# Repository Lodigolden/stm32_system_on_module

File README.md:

# STM32H7 System-on-Module
## Overview
This STM32H7 system-on-module is everything needed to get the MCU up and running. Simply place a footprint for the board-to-board connectors on your motherboard, and use whatever pins your project needs!

## Hardware
The system-on-module is a powerful compute source with everything you need for intensive computation. Peripherals include:
- STM32H743ZGT6 32Bit MCU
- AS4C8M16SA-7TCN 128MBit SDRAM
- AT25FF161A-SSHN-T 16MBit QSPI Flash
- CP2102N-A02-GQFN20R USB-to-UART Bridge

The system on module has a point-of-load regulator (TPSM861253RDXR) to ensure stable, efficient power delivery to on-board peripherals.

## Firmware
Included in this repository is a device tree file and other necessary files for building a zephyr image. The **fw/** README.md file gives instructions for building on a Linux system.

> TODO: Write instructions for Windows use.

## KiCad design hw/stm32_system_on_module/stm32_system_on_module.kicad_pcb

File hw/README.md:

# Overview
The **pinout/** directory includes an STMCubeIDE file used to deetermine pinouts for the on-board components. If the end user doesn't wish to use Zephyr and would rather use STMCubeIDE, they can feel free to start with that folder.

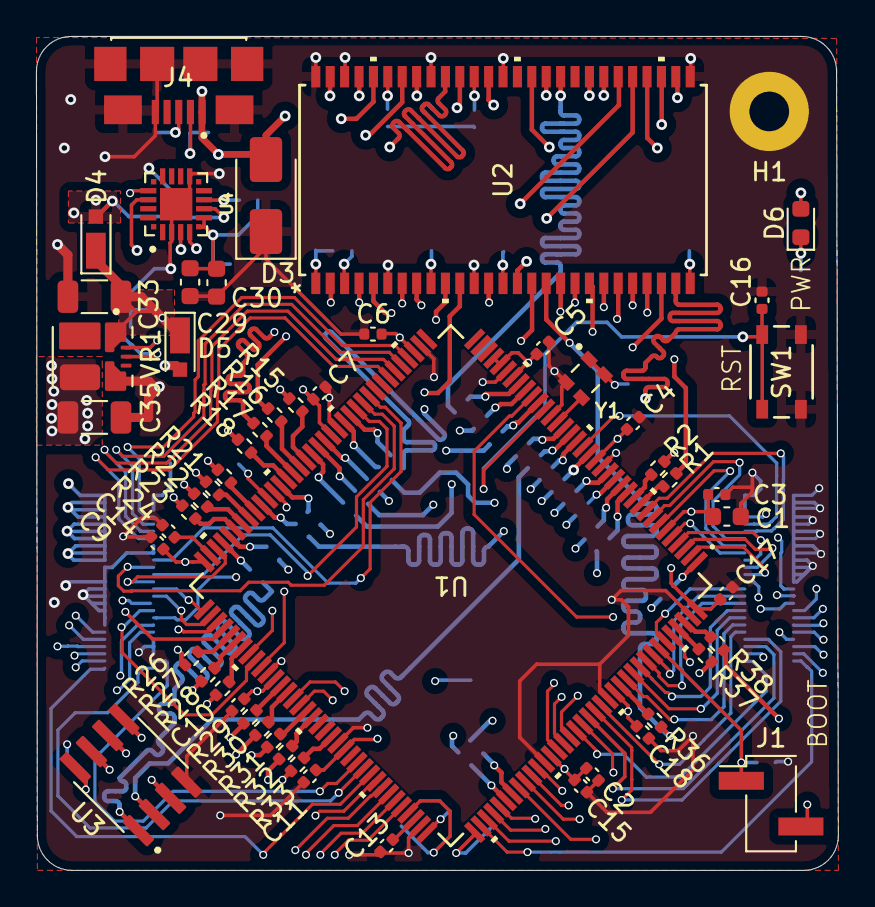
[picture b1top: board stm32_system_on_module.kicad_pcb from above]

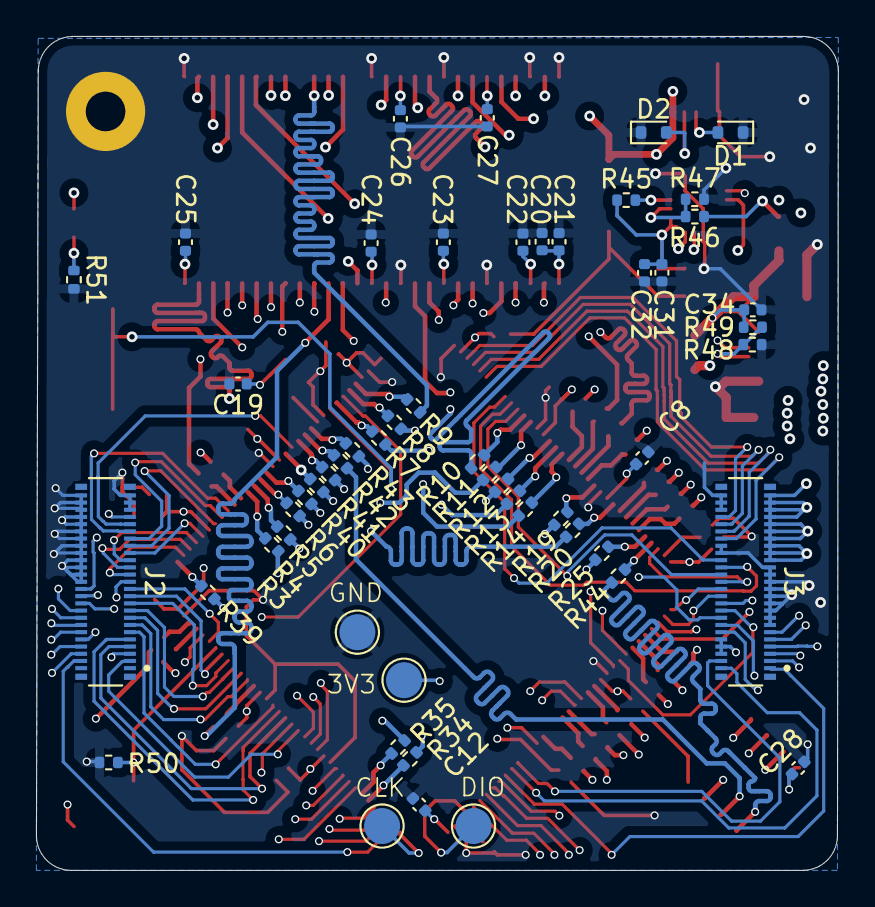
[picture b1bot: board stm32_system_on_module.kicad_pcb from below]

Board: 8 copper layers, 44.6 x 46.3 mm, 108 parts (53 on the bottom side), 163 nets.

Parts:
C1, C29, C30: 4u7; C_0603_1608Metric
C2, C20: 1u; C_0402_1005Metric
C3, C4, C5, C6, C7, C8, C9, C10, C11, C12, C13, C14, C15, C16, C17, C18, C19, C21, C22, C23, C24, C25, C26, C27, C28, C31, C32, C34: 100n; C_0402_1005Metric
C33: 10u; C_1206_3216Metric
C35: 22u; C_1206_3216Metric
D1, D2: D_TVS; D_SOD-523
D3: D_TVS; D_SMA
D4, D5: D_Schottky; D_MicroSMP_AK
D6: LED; LED_0603_1608Metric
H1: MountingHole_Pad; MountingHole_2.2mm_M2_Pad
J1: Conn_01x02_Pin; PinHeader_1x02_P2.54mm_Vertical_SMD_Pin1Left
J2, J3: DF40C-50DP-0.4V_51_; HIROSE_DF40C-50DP-0.4V_51_
J4: 10118192-0002LF; AMPHENOL_10118192-0002LF
R1, R2, R3, R4, R5, R6, R7, R8, R9, R10, R11, R12, R13, R14, R15, R16, R17, R18, R19, R20, R21, R22, R23, R24, R25, R26, R27, R28, R29, R30, R31, R32, R33, R34, R35, R36, R37, R38, R39, R40, R41, R42, R43, R44: 33; R_0402_1005Metric
R45: 1k; R_0402_1005Metric
R46: 22k1; R_0402_1005Metric
R47: 47k5; R_0402_1005Metric
R48: 4k99; R_0402_1005Metric
R49, R50: 10k; R_0402_1005Metric
R51: 330; R_0402_1005Metric
SW1: PTS810 SJK 250 SMTR LFS; PTS810_CNK
TP1, TP2, TP3, TP4: TestPoint; TestPoint_Pad_D2.0mm
U1: STM32H743ZGT6; stm32h743zgt6
U2: AS4C8M16SA-7TCN; TSOP-54_11P96X22P35_ALL
U3: AT25FF161A-SSHN-T; SOIC127P599X175-8N
U4: CP2102N-A02-GQFN20R; SILABS_CP2102N-A02-GQFN20R
VR1: TPSM861253RDXR; VREG_TPSM861253RDXR
Y1: KC2016Z8.00000C15XXK; OSC_KC2016Z8.00000C15XXK-4

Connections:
+3V3: C1.1, C2.1, C3.1, C4.1, C5.1, C6.1, C7.1, C8.1, C9.1, C10.1, C11.1, C12.1, C15.1, C17.1, C18.1, C19.1, C20.1, C21.1, C22.1, C23.1, C24.1, C25.1, C26.1, C27.1, C28.1, C29.1, C30.1, C31.1, C32.1, C35.1, D6.2 (A), J1.2, R45.1, TP3.1, U1.6 (VBAT), U1.17 (VDD), U1.30 (VDD), U1.32 (VREF+), U1.33 (VDDA), U1.39 (VDD), U1.52 (VDD), U1.62 (VDD), U1.72 (VDD), U1.84 (VDD), U1.95 (VDD33USB), U1.108 (VDD), U1.121 (VDD), U1.131 (VDD), U1.144 (VDD), U2.1 (VDD), U2.3 (VDDQ), U2.9 (VDDQ), U2.14 (VDD), U2.27 (VDD), U2.43 (VDDQ), U2.49 (VDDQ), U3.8 (VCC), U4.6 (VDD), U4.7 (VREGIN), VR1.3 (VOUT), VR1.7 (VOS), Y1.1 (INH), Y1.4 (VCC)
+5V: D3.2 (A2), D4.2 (A), J4.1 (VCC), R46.1
/Input/USB.D+: D1.2 (A2), J4.3 (D+), U4.4 (D+)
/Input/USB.D-: D2.2 (A2), J4.2 (D-), U4.5 (D-)
/MCU/BOOT: J1.1, R50.1, U1.138 (BOOT0)
/MCU/NRST: C16.1, SW1.1, SW1.2, U1.25 (NRST)
/MCU/OSC_IN: U1.23 (OSC_IN), Y1.3 (OUTPUT)
/MCU/SWD.CLK: TP2.1, U1.109 (PA14)
/MCU/SWD.DIO: TP1.1, U1.105 (PA13)
FMC.A0: R1.2, U2.23 (A0)
FMC.A1: R2.2, U2.24 (A1)
FMC.A2: R3.2, U2.25 (A2)
FMC.A3: R4.2, U2.26 (A3)
FMC.A4: R5.2, U2.29 (A4)
FMC.A5: R6.2, U2.30 (A5)
FMC.A6: R11.2, U2.31 (A6)
FMC.A7: R12.2, U2.32 (A7)
FMC.A8: R13.2, U2.33 (A8)
FMC.A9: R14.2, U2.34 (A9)
FMC.A10: R15.2, U2.22 (A10/AP)
FMC.A11: R16.2, U2.35 (A11)
FMC.BA0: R31.2, U2.20 (BA0)
FMC.BA1: R32.2, U2.21 (BA1)
FMC.D0: R29.2, U2.2 (DQ0)
FMC.D1: R30.2, U2.4 (DQ1)
FMC.D2: R34.2, U2.5 (DQ2)
FMC.D3: R35.2, U2.7 (DQ3)
FMC.D4: R17.2, U2.8 (DQ4)
FMC.D5: R18.2, U2.10 (DQ5)
FMC.D6: R19.2, U2.11 (DQ6)
FMC.D7: R20.2, U2.13 (DQ7)
FMC.D8: R21.2, U2.42 (DQ8)
FMC.D9: R22.2, U2.44 (DQ9)
FMC.D10: R23.2, U2.45 (DQ10)
FMC.D11: R24.2, U2.47 (DQ11)
FMC.D12: R25.2, U2.48 (DQ12)
FMC.D13: R26.2, U2.50 (DQ13)
FMC.D14: R27.2, U2.51 (DQ14)
FMC.D15: R28.2, U2.53 (DQ15)
FMC.NBL0: R37.2, U2.15 (LDQM)
FMC.NBL1: R38.2, U2.39 (UDQM)
FMC.SDCKE0: R9.2, U2.37 (CKE)
FMC.SDCLK: R33.2, U2.38 (CLK)
FMC.SDNCAS: R36.2, U2.17 (*CAS)
FMC.SDNE0: R8.2, U2.19 (*CS)
FMC.SDNRAS: R10.2, U2.18 (*RAS)
FMC.SDNWE: R7.2, U2.16 (*WE)
GND: C1.2, C2.2, C3.2, C4.2, C5.2, C6.2, C7.2, C8.2, C9.2, C10.2, C11.2, C12.2, C13.2, C14.2, C15.2, C16.2, C17.2, C18.2, C19.2, C20.2, C21.2, C22.2, C23.2, C24.2, C25.2, C26.2, C27.2, C28.2, C29.2, C30.2, C31.2, C32.2, C33.2, C34.2, C35.2, D1.1 (A1), D2.1 (A1), D3.1 (A1), H1.1, J2.26, J2.28, J2.30, J2.32, J2.34, J2.36, J2.38, J2.40, J2.42, J2.44, J2.45, J2.46, J2.47, J2.48, J2.49, J2.50, J3.6, J3.8, J3.10, J3.13, J3.15, J3.17, J3.19, J3.21, J3.23, J3.25, J3.27, J3.29, J3.34, J3.36, J3.46, J3.48, J3.50, J4.5 (GND), J4.S1 (SHIELD), J4.S2 (SHIELD), J4.S3 (SHIELD), J4.S4 (SHIELD), J4.S5 (SHIELD), J4.S6 (SHIELD), R47.2, R48.2, R50.2, R51.2, SW1.3, SW1.4, TP4.1, U1.16 (VSS), U1.24 (OSC_OUT), U1.31 (VSSA), U1.38 (VSS), U1.51 (VSS), U1.61 (VSS), U1.83 (VSS), U1.94 (VSS), U1.107 (VSS), U1.120 (VSS), U1.130 (VSS), U1.143 (PDR_ON), U2.6 (VSSQ), U2.12 (VSSQ), U2.28 (VSS), U2.41 (VSS), U2.46 (VSSQ), U2.52 (VSSQ), U2.54 (VSS), U3.4 (GND), U4.3 (GND), U4.12 (GND), U4.21 (GND), VR1.4 (PGND), Y1.2 (CASE_GND)
LINE: C33.1, C34.1, D4.1 (K), D5.1 (K), R49.1, VR1.1 (VIN)
unnamed: C13.1, U1.106 (VCAP)
unnamed: C14.1, U1.71 (VCAP)
unnamed: D6.1 (K), R51.1
unnamed: R44.1, U1.69 (PB10)
unnamed: R7.1, U1.26 (PC0)
unnamed: R8.1, U1.28 (PC2)
unnamed: R9.1, U1.29 (PC3)
unnamed: R34.1, U1.114 (PD0)
unnamed: R35.1, U1.115 (PD1)
unnamed: R26.1, U1.77 (PD8)
unnamed: R27.1, U1.78 (PD9)
unnamed: R28.1, U1.79 (PD10)
unnamed: R29.1, U1.85 (PD14)
unnamed: R30.1, U1.86 (PD15)
unnamed: R37.1, U1.141 (PE0)
unnamed: R38.1, U1.142 (PE1)
unnamed: R39.1, U1.1 (PE2)
unnamed: R17.1, U1.58 (PE7)
unnamed: R18.1, U1.59 (PE8)
unnamed: R19.1, U1.60 (PE9)
unnamed: R20.1, U1.63 (PE10)
unnamed: R21.1, U1.64 (PE11)
unnamed: R22.1, U1.65 (PE12)
unnamed: R23.1, U1.66 (PE13)
unnamed: R24.1, U1.67 (PE14)
unnamed: R25.1, U1.68 (PE15)
unnamed: R1.1, U1.10 (PF0)
unnamed: R2.1, U1.11 (PF1)
unnamed: R3.1, U1.12 (PF2)
unnamed: R4.1, U1.13 (PF3)
unnamed: R5.1, U1.14 (PF4)
unnamed: R6.1, U1.15 (PF5)
unnamed: R40.1, U1.18 (PF6)
unnamed: R41.1, U1.20 (PF8)
unnamed: R42.1, U1.21 (PF9)
unnamed: R43.1, U1.22 (PF10)
unnamed: R10.1, U1.49 (PF11)
unnamed: R11.1, U1.50 (PF12)
unnamed: R12.1, U1.53 (PF13)
unnamed: R13.1, U1.54 (PF14)
unnamed: R14.1, U1.55 (PF15)
unnamed: R15.1, U1.56 (PG0)
unnamed: R16.1, U1.57 (PG1)
unnamed: R31.1, U1.89 (PG4)
unnamed: R32.1, U1.90 (PG5)
unnamed: R33.1, U1.93 (PG8)
unnamed: R36.1, U1.132 (PG15)
unnamed: R46.2, R47.1, U4.8 (VBUS)
unnamed: R45.2, U4.9 (~RST)
unnamed: R48.1, R49.2, VR1.6 (EN)
PA.4: J3.44, U1.40 (PA4)
PA.5: J3.42, U1.41 (PA5)
PA.6: J3.40, U1.42 (PA6)
PA.7: J3.38, U1.43 (PA7)
PA.8: J3.3, U1.100 (PA8)
PA.9: J3.5, U1.101 (PA9)
PA.10: J3.7, U1.102 (PA10)
PA.11: J3.9, U1.103 (PA11)
PA.12: J3.11, U1.104 (PA12)
PA.15: J2.4, U1.110 (PA15)
PB.0: J3.32, U1.46 (PB0)
PB.1: J3.30, U1.47 (PB1)
PB.2: J3.28, U1.48 (PB2)
PB.3: J2.13, U1.133 (PB3)
PB.4: J2.15, U1.134 (PB4)
PB.5: J2.17, U1.135 (PB5)
PB.6: J2.19, U1.136 (PB6)
PB.7: J2.21, U1.137 (PB7)
PB.8: J2.23, U1.139 (PB8)
PB.9: J2.25, U1.140 (PB9)
PB.11: J3.26, U1.70 (PB11)
PB.12: J3.24, U1.73 (PB12)
PB.13: J3.22, U1.74 (PB13)
PC.1: J2.43, U1.27 (PC1)
PC.7: J3.4, U1.97 (PC7)
PC.8: J3.2, U1.98 (PC8)
PC.9: J3.1, U1.99 (PC9)
PC.10: J2.6, U1.111 (PC10)
PC.11: J2.8, U1.112 (PC11)
PC.12: J2.10, U1.113 (PC12)
PC.13: J2.35, U1.7 (PC13)
PC.14: J2.37, U1.8 (PC14)
PC.15: J2.39, U1.9 (PC15)
PD.2: J2.12, U1.116 (PD2)
PD.3: J2.14, U1.117 (PD3)
PD.4: J2.16, U1.118 (PD4)
PD.5: J2.18, U1.119 (PD5)
PD.6: J2.24, U1.122 (PD6)
PD.7: J2.22, U1.123 (PD7)
PD.11: J3.20, U1.80 (PD11)
PD.12: J3.18, U1.81 (PD12)
PD.13: J3.16, U1.82 (PD13)
PE.3: J2.27, U1.2 (PE3)
PE.4: J2.29, U1.3 (PE4)
PE.5: J2.31, U1.4 (PE5)
PE.6: J2.33, U1.5 (PE6)
PF.7: J2.41, U1.19 (PF7)
PG.2: J3.14, U1.87 (PG2)
PG.3: J3.12, U1.88 (PG3)
PG.9: J2.20, U1.124 (PG9)
PG.10: J2.3, U1.125 (PG10)
PG.11: J2.5, U1.126 (PG11)
PG.12: J2.7, U1.127 (PG12)
PG.13: J2.9, U1.128 (PG13)
PG.14: J2.11, U1.129 (PG14)
QSPI.CLK: R43.2, U3.6 (SCK)
QSPI.IO0: R41.2, U3.5 (SI(I/O0))
QSPI.IO1: R42.2, U3.2 (SO(I/O1))
QSPI.IO2: R39.2, U3.3 (~WP)
QSPI.IO3: R40.2, U3.7 (~HOLD)
QSPI.NCS: R44.2, U3.1 (~CS)
UART.RX: U1.76 (PB15), U4.18 (TXD)
UART.TX: U1.75 (PB14), U4.17 (RXD)
VBUS: D5.2 (A), J3.31, J3.33, J3.35, J3.37, J3.39, J3.41, J3.43, J3.45, J3.47, J3.49

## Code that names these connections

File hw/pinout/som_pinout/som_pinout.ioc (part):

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Mcu.Name=STM32H743ZGTx
Mcu.Package=LQFP144
Mcu.UserName=STM32H743ZGTx
PA13\ (JTMS/SWDIO).Mode=Serial_Wire
PA13\ (JTMS/SWDIO).Signal=DEBUG_JTMS-SWDIO
PA14\ (JTCK/SWCLK).Mode=Serial_Wire
PA14\ (JTCK/SWCLK).Signal=DEBUG_JTCK-SWCLK
PB10.Mode=Single Bank 1
PB10.Signal=QUADSPI_BK1_NCS
PB14.Mode=Asynchronous
PB14.Signal=USART1_TX
PB15.Mode=Asynchronous
PB15.Signal=USART1_RX
PC0.Signal=FMC_SDNWE
PC2_C.Mode=SdramChipSelect1_1
PC2_C.Signal=FMC_SDNE0
PC3_C.Mode=SdramChipSelect1_1
PC3_C.Signal=FMC_SDCKE0
PD0.Signal=FMC_D2_DA2
PD1.Signal=FMC_D3_DA3
PD10.Signal=FMC_D15_DA15
PD14.Signal=FMC_D0_DA0
PD15.Signal=FMC_D1_DA1
PD8.Signal=FMC_D13_DA13
PD9.Signal=FMC_D14_DA14
PE0.Signal=FMC_NBL0
PE1.Signal=FMC_NBL1
PE10.Signal=FMC_D7_DA7
PE11.Signal=FMC_D8_DA8
PE12.Signal=FMC_D9_DA9
PE13.Signal=FMC_D10_DA10
PE14.Signal=FMC_D11_DA11
PE15.Signal=FMC_D12_DA12
PE2.Mode=Single Bank 1
PE2.Signal=QUADSPI_BK1_IO2
PE7.Signal=FMC_D4_DA4
PE8.Signal=FMC_D5_DA5
PE9.Signal=FMC_D6_DA6
PF0.Signal=FMC_A0
PF1.Signal=FMC_A1
PF10.Mode=Single Bank 1
PF10.Signal=QUADSPI_CLK
PF11.Signal=FMC_SDNRAS
PF12.Signal=FMC_A6
PF13.Signal=FMC_A7
PF14.Signal=FMC_A8
PF15.Signal=FMC_A9
PF2.Signal=FMC_A2
PF3.Signal=FMC_A3
PF4.Signal=FMC_A4
PF5.Signal=FMC_A5
PF6.Mode=Single Bank 1
PF6.Signal=QUADSPI_BK1_IO3
PF8.Mode=Single Bank 1
PF8.Signal=QUADSPI_BK1_IO0
PF9.Mode=Single Bank 1
PF9.Signal=QUADSPI_BK1_IO1
PG0.Signal=FMC_A10
PG1.Signal=FMC_A11
PG15.Signal=FMC_SDNCAS
PG4.Signal=FMC_A14_BA0
PG5.Signal=FMC_A15_BA1
PG8.Signal=FMC_SDCLK
PH0-OSC_IN\ (PH0).Mode=HSE-External-Oscillator
PH0-OSC_IN\ (PH0).Signal=RCC_OSC_IN
PH1-OSC_OUT\ (PH1).Mode=HSE-External-Oscillator
PH1-OSC_OUT\ (PH1).Signal=RCC_OSC_OUT
RCC.HSE_VALUE=8000000
RCC.SYSCLKFreq_VALUE=64000000
board=custom

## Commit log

2026-04-02 schematic and layout progress
2026-05-26 HW finished
2026-05-27 Started fw development
2026-06-04 Added flash driver
2026-06-04 Cleaned up repo
2026-06-04 Cleanup
2026-06-06 SDRAM support added
2026-06-07 Final polishing on the repo + TODOs
2026-06-07 Repo clean-up
2026-06-07 Added HW schematic
2026-06-09 Added BoM
